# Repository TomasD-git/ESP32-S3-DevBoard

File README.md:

# ESP32-S3-DevBoard
**Normal ESP32 S3 DevBoard, supports any firmware of normal esp32 s3, has antenna**    

<details>
<summary>BOM</summary>

| BOM Name | Purpose | Quantity | Total Cost (USD) | Link | Distributor |
|---|---|---|---|---|---|
| PCB + stencil | all components are on this | 1 | 17 | https://jlcpcb.com | jlcpcb |
| ALL components | all components that are on pcb | 1 | 20 | https://lcsc.com | lcsc |
| | | Total cost | 37 | | |

</details>

# Pictures  
**Schematic**   
  
**PCB**  
  
**3D Viewer (Top view)**    
  
**3D Viewer (Bottom view)**

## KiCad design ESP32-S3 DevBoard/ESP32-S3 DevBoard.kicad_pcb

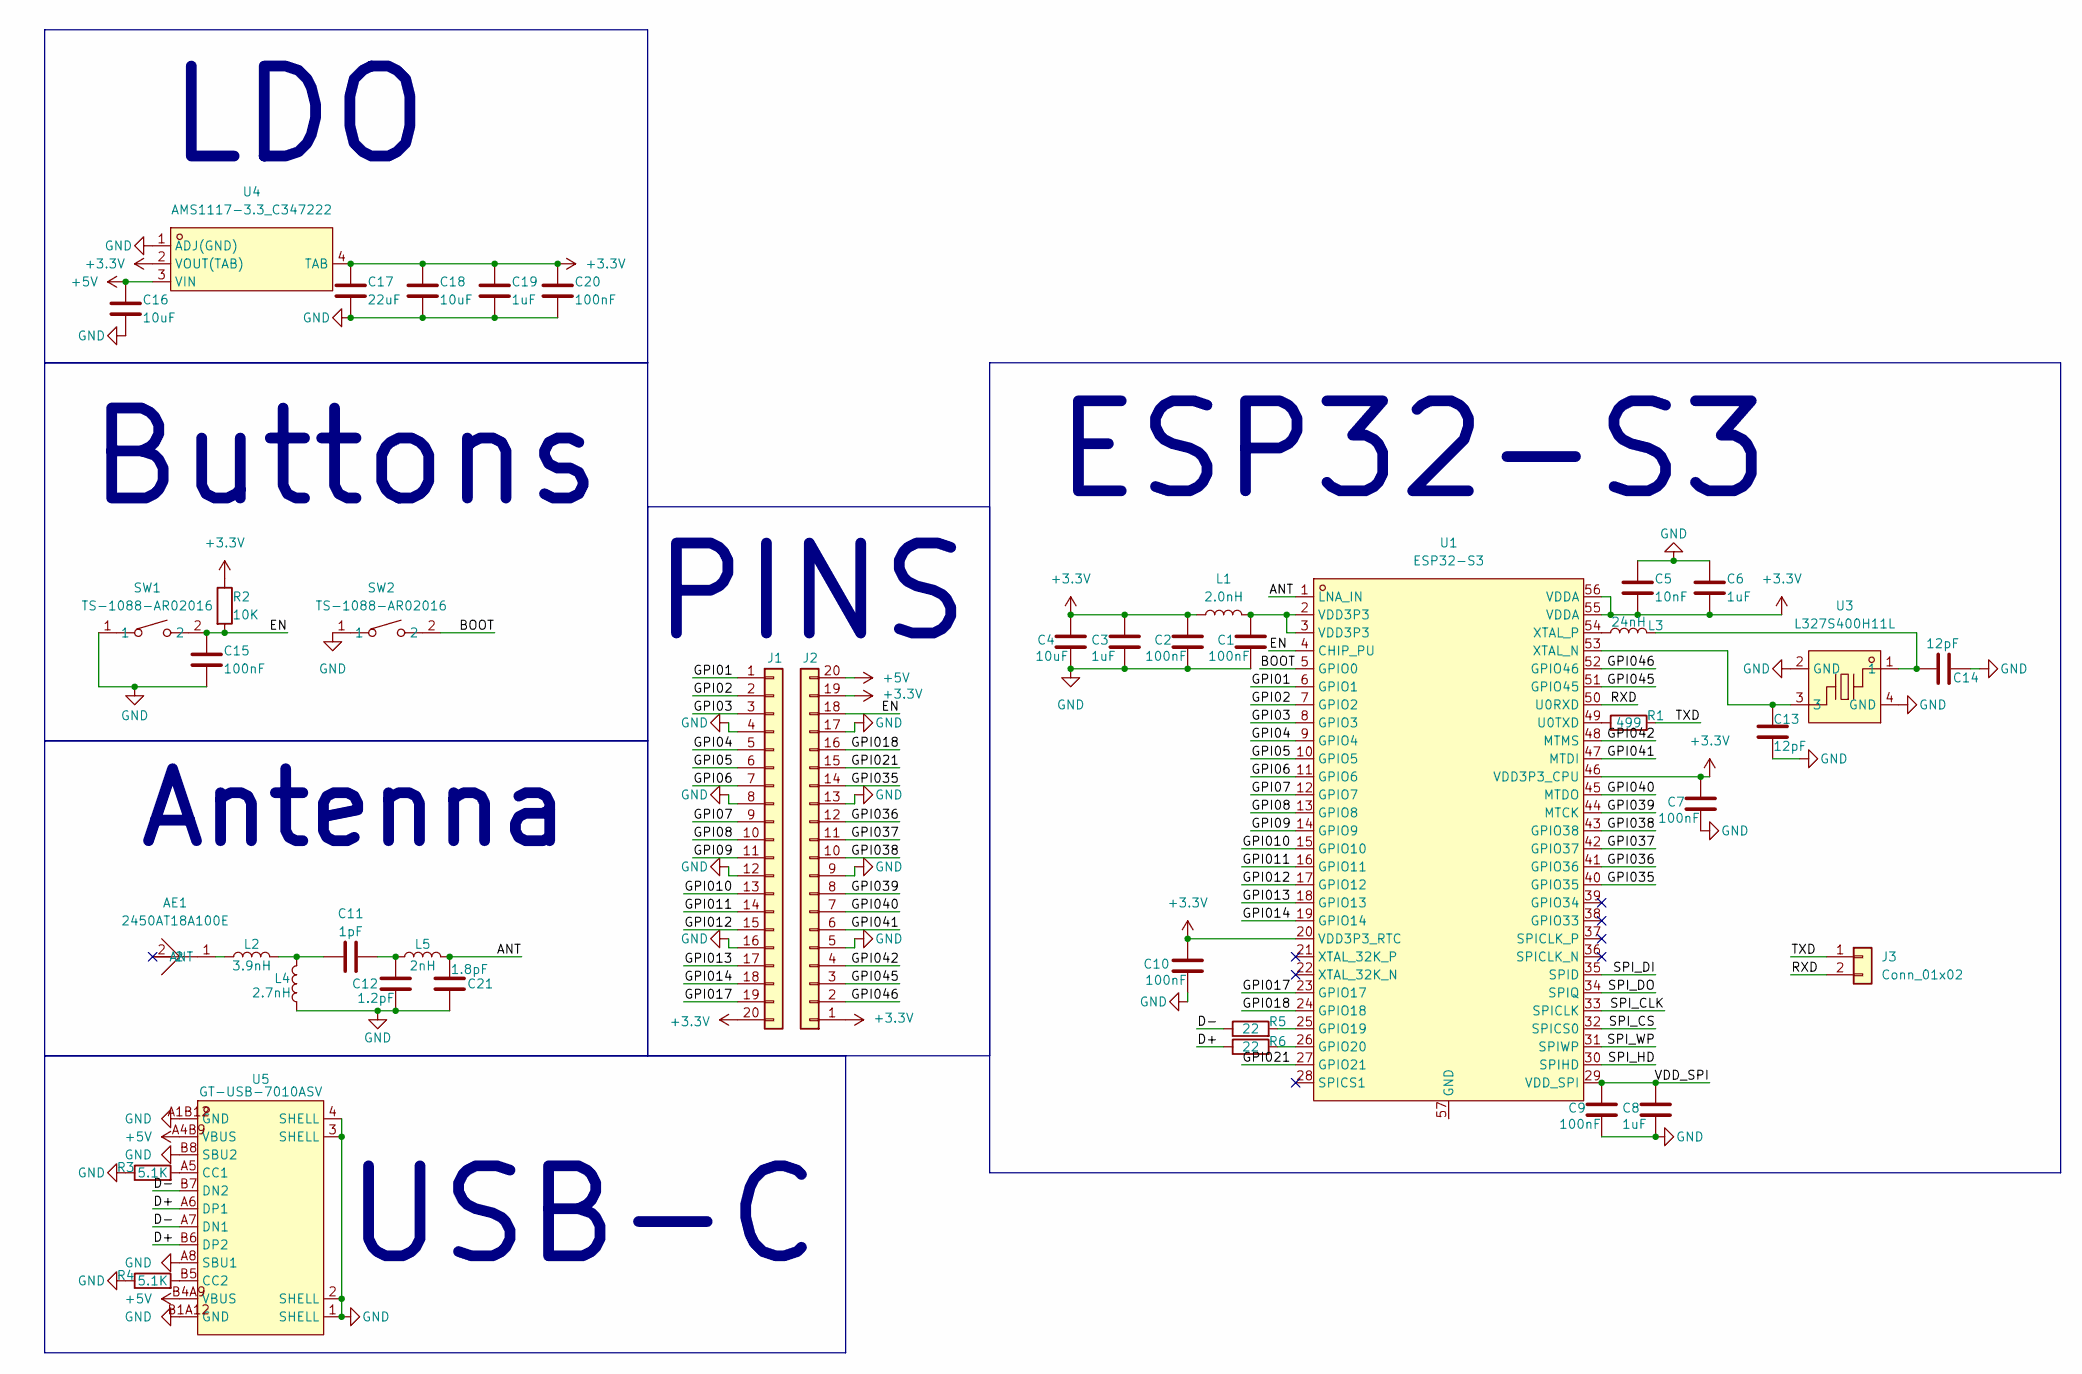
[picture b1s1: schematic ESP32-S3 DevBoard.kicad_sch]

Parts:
AE1: 2450AT18A100E; ANT-SMD_L3.2-W1.6; MPN 2450AT18A100E; LCSC Part C89334
C1, C2, C7, C9, C10, C15, C20: 100nF; C_0201_0603Metric
C3, C6, C8, C19: 1uF; C_0402_1005Metric
C4, C16, C18: 10uF; C_0603_1608Metric
C5: 10nF; C_0201_0603Metric
C11: 1pF; C_0201_0603Metric
C12: 1.2pF; C_0201_0603Metric
C13, C14: 12pF; C_0201_0603Metric
C17: 22uF; C_0805_2012Metric
C21: 1.8pF; C_0201_0603Metric
J1, J2: Conn_01x20; PinHeader_1x20_P2.54mm_Vertical
J3: Conn_01x02; PinHeader_1x02_P2.54mm_Vertical
L1: 2.0nH; L_0201_0603Metric
L2: 3.9nH; L_0201_0603Metric
L3: 24nH; L_0201_0603Metric
L4: 2.7nH; L_0201_0603Metric
L5: 2nH; L_0201_0603Metric
R1: 499; R_0201_0603Metric
R2: 10K; R_0201_0603Metric
R3, R4: 5.1K; R_0201_0603Metric
R5, R6: 22; R_0201_0603Metric
SW1, SW2: TS-1088-AR02016; SW-SMD_L3.9-W3.0-P4.45; MPN TS-1088-AR02016; LCSC Part C720477
U1: ESP32-S3; QFN-56_L7.0-W7.0-P0.40-TL-EP4.0; MPN ESP32-S3R8; LCSC Part C2913194
U3: L327S400H11L; CRYSTAL-SMD_4P-L3.2-W2.5-BL; MPN L327S400H11L; LCSC Part C5261245
U4: AMS1117-3.3_C347222; SOT-223-4_L6.5-W3.5-P2.30-LS7.0-BR; MPN AMS1117-3.3; LCSC Part C347222
U5: GT-USB-7010ASV; USB-C-SMD_G-SWITCH_GT-USB-7010ASV; MPN GT-USB-7010ASV; LCSC Part C2988369

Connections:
+3.3V: C2.1, C3.1, C4.1, C5.2, C6.2, C7.1, C10.1, C17.1, C18.1, C19.1, C20.1, J1.20, J2.1, J2.19, L1.1, R2.1, U1.20 (VDD3P3_RTC), U1.46 (VDD3P3_CPU), U1.55 (VDDA), U1.56 (VDDA), U4.2 (VOUT(TAB)), U4.4 (TAB)
+5V: C16.1, J2.20, U4.3 (VIN), U5.A4B9 (VBUS), U5.B4A9 (VBUS)
/ANT: C21.2, L5.2, U1.1 (LNA_IN)
/BOOT: SW2.2, U1.5 (GPIO0)
/D+: R6.1, U5.A6 (DP1), U5.B6 (DP2)
/D-: R5.1, U5.A7 (DN1), U5.B7 (DN2)
/EN: C15.1, J2.18, R2.2, SW1.2, U1.4 (CHIP_PU)
/GPI01: J1.1, U1.6 (GPIO1)
/GPI02: J1.2, U1.7 (GPIO2)
/GPI03: J1.3, U1.8 (GPIO3)
/GPI04: J1.5, U1.9 (GPIO4)
/GPI05: J1.6, U1.10 (GPIO5)
/GPI06: J1.7, U1.11 (GPIO6)
/GPI07: J1.9, U1.12 (GPIO7)
/GPI08: J1.10, U1.13 (GPIO8)
/GPI09: J1.11, U1.14 (GPIO9)
/GPI010: J1.13, U1.15 (GPIO10)
/GPI011: J1.14, U1.16 (GPIO11)
/GPI012: J1.15, U1.17 (GPIO12)
/GPI013: J1.17, U1.18 (GPIO13)
/GPI014: J1.18, U1.19 (GPIO14)
/GPI017: J1.19, U1.23 (GPIO17)
/GPI018: J2.16, U1.24 (GPIO18)
/GPI021: J2.15, U1.27 (GPIO21)
/GPI035: J2.14, U1.40 (GPIO35)
/GPI036: J2.12, U1.41 (GPIO36)
/GPI037: J2.11, U1.42 (GPIO37)
/GPI038: J2.10, U1.43 (GPIO38)
/GPI039: J2.8, U1.44 (MTCK)
/GPI040: J2.7, U1.45 (MTDO)
/GPI041: J2.6, U1.47 (MTDI)
/GPI042: J2.4, U1.48 (MTMS)
/GPI045: J2.3, U1.51 (GPIO45)
/GPI046: J2.2, U1.52 (GPIO46)
/RXD: J3.2, U1.50 (U0RXD)
/SPI_CLK: U1.33 (SPICLK)
/SPI_CS: U1.32 (SPICS0)
/SPI_DI: U1.35 (SPID)
/SPI_DO: U1.34 (SPIQ)
/SPI_HD: U1.30 (SPIHD)
/SPI_WP: U1.31 (SPIWP)
/TXD: J3.1, R1.2
/VDD_SPI: C8.1, C9.1, U1.29 (VDD_SPI)
GND: C1.2, C2.2, C3.2, C4.2, C5.1, C6.1, C7.2, C8.2, C9.2, C10.2, C12.2, C13.2, C14.2, C15.2, C16.2, C17.2, C18.2, C19.2, C20.2, C21.1, J1.4, J1.8, J1.12, J1.16, J2.5, J2.9, J2.13, J2.17, L4.1, R3.1, R4.1, SW1.1, SW2.1, U3.2 (GND), U3.4 (GND), U4.1 (ADJ(GND)), U5.1 (SHELL), U5.2 (SHELL), U5.3 (SHELL), U5.4 (SHELL), U5.A1B12 (GND), U5.A8 (SBU1), U5.B1A12 (GND), U5.B8 (SBU2)
unnamed: AE1.1 (ANT), L2.1
unnamed: C1.1, L1.2, U1.2 (VDD3P3), U1.3 (VDD3P3)
unnamed: C11.1, C12.1, L5.1
unnamed: C11.2, L2.2, L4.2
unnamed: C14.1, L3.2, U3.1
unnamed: R5.2, U1.25 (GPIO19)
unnamed: R6.2, U1.26 (GPIO20)
unnamed: R1.1, U1.49 (U0TXD)
unnamed: C13.1, U1.53 (XTAL_N), U3.3
unnamed: L3.1, U1.54 (XTAL_P)
unnamed: R3.2, U5.A5 (CC1)
unnamed: R4.2, U5.B5 (CC2)

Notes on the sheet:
Antenna
LDO
Buttons
ESP32-S3
PINS
USB-C

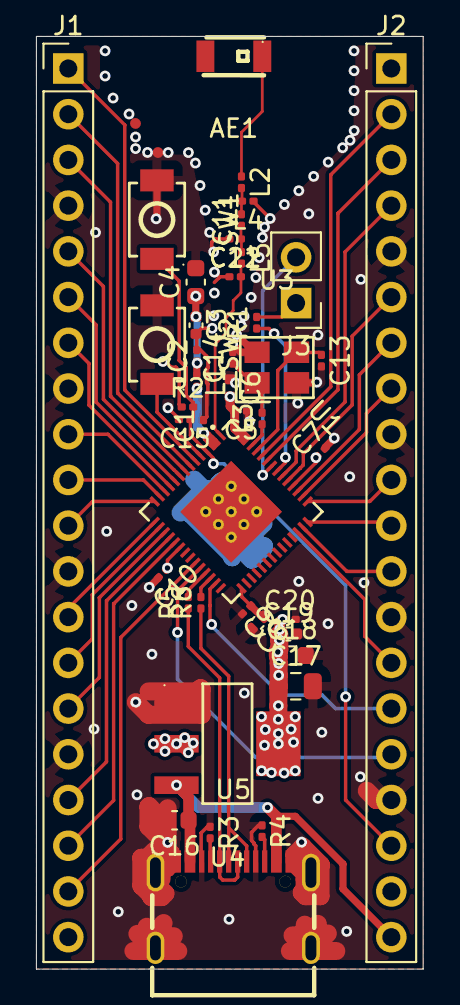
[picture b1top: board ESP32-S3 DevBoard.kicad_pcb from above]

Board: 4 copper layers, 21.5 x 51.8 mm, 42 parts (0 on the bottom side), 50 nets.

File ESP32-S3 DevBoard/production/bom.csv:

Designator,Footprint,Quantity,Value,LCSC Part #
AE1,ANT-SMD_L3.2-W1.6,1,2450AT18A100E,C89334
"C1, C10, C15, C2, C20, C7, C9",0201,7,100nF,C190183
C11,0201,1,1pF,C85893
C12,0201,1,1.2pF,C22374839
"C13, C14",0201,2,11pF,C384958
"C16, C18, C4",0603,3,10uF,C711098
C17,0805,1,22uF,C98190
"C19, C3, C6, C8",0402,4,1uF,C106254
C21,0201,1,1.8pF,C22374841
C5,0201,1,10nF,C272853
"J1, J2",PinHeader_1x20_P2.54mm_Vertical,2,Conn_01x20,
J3,PinHeader_1x02_P2.54mm_Vertical,1,Conn_01x02,
L1,0201,1,2.0nH,C86125
L2,0201,1,3.9nH,C76756
L3,0201,1,24nH,C275178
L4,0201,1,2.7nH,C7216765
L5,0201,1,2nH,C86125
R1,0201,1,499,C138137
R2,0201,1,10K,C473048
"R3, R4",0201,2,5.1K,C270344
"R5, R6",0201,2,22,C142011
"SW1, SW2",SW-SMD_L3.9-W3.0-P4.45,2,TS-1088-AR02016,C720477
U1,QFN-56_L7.0-W7.0-P0.40-TL-EP4.0,1,ESP32-S3,C2913194
U3,CRYSTAL-SMD_4P-L3.2-W2.5-BL,1,L327S400H11L,C5261245
U4,SOT-223-4_L6.5-W3.5-P2.30-LS7.0-BR,1,AMS1117-3.3_C347222,C347222
U5,USB-C-SMD_G-SWITCH_GT-USB-7010ASV,1,GT-USB-7010ASV,C2988369
